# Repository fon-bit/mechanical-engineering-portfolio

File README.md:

# Engineering Portfolio

Welcome! This repository showcases selected ME coursework and personal engineering projects.

Each project folder contains:
- Project Report 
- Supporting files (data, presentations, photos)
- A README with project overview

---

## 📂 Projects

### 🔹 [Capstone Project – Nova Spot Micro 3](Capstone_Project_NovaSpotMicro3/README.md)
- **Objective:** Prototype a quadruped robot using a pre-built frame and motors (Nova SM3)
- **My Role:** 3D modeled the frame in Fusion360/Ansys, ran stress analysis in Ansys, simulated walking in software
- **Tools:** Fusion360, ANSYS, 3D printing  
- **Outcome:** Completed a functional robot prototype capable of walking and surrounding detection  

---

### 🔹 [JanKey40](JanKey40/README.md)
- **Objective:** Create custom keyboard from scratch!
- **Tools:** KiCad, Fusion 360  
- **Deliverables:** Design and create case, pcb, and plate for 40% keyboard!

---

### 🔹 [Transient Simulation](Transient_Simulation/README.md)
- **Objective:** Simulated 2D heat conduction in a material with varying boundary conditions
- **Tools:** ANSYS  
- **Deliverables:** Report how to use transient simulation to show results at specific time and show quantitative results

---

### 🔹 [Bracket Static Structural Study](FEA/README.md)
- **Objective:** Using FEA to analyze a bracket
- **Tools:** ANSYS  
- **Deliverables:** Report showing the understanding of FEA and how to solve for results

---

### 🔹 [Ansys Modal Analysis](Modal_Analysis/README.md)
- **Objective:** Perform a modal analysis on a bracket
- **Tools:** ANSYS
- **Deliverables:** Report showing the understanding of modal analysis and how to solve natural frequencies in a system
  
---

### 🔹 [Fluid CFD Course Project](CFD_Project/README.md)
- **Objective:** Analyze fluid flow and heat transfer in a system. Understand ANSYS software and interpret data results
- **Tools:** ANSYS
- **Deliverables:** Report summarizing data and understanding of CFD

---

## 📬 Contact
Feel free to connect with me on [LinkedIn](https://www.linkedin.com/in/fontanna-vo-6ab0a2368/) or via email: **fontanna_vo@aol.com**.

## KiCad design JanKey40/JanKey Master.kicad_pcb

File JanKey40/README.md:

**JanKey40**

*40% Mechanical Keyboard PCB*

## Overview
This is a personal passion of mine and I've always wanted to try a 40% keyboard and instead of spending $150+ on a prebuilt I decided to spend 150hrs and even more money on building a custom one! All joking aside this has been a passion of mine for a while and I wanted to share with the world my journey in the world of custom keyboards. As of now I'm in the design phase for the case, the pcb is currently under review at the manufactors!! Check at the files and images for this project and feel free to leave me some feedback!

## Objectives
- Designed a custom 40% mechanical keyboard from scratch
- Designed in KiCad, manufacturable PCB (*manufactuered approve*)
- Case design using Fusion360 (*under review @manufactures*)

## Deliverables
- 40% keyboard PCB
- Custom Case Design 
- Final Assembly of keyboard

## 3D Rendered View

https://github.com/user-attachments/assets/bd2a3828-73c8-46a6-a715-73c00b7ea09d

*Case material: anodized aluminum blue (top case) anodized aluminum red (bottom case render)* 

## PHOTOS

**Current files include PCB schematics, pcb and project from KiCad (feel free to download and create your own!)**

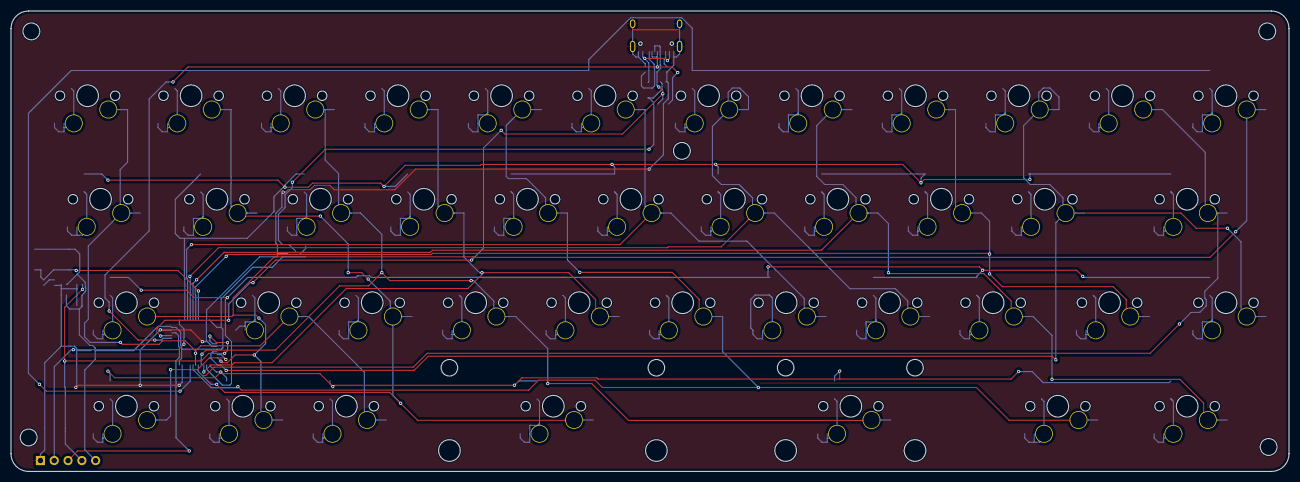
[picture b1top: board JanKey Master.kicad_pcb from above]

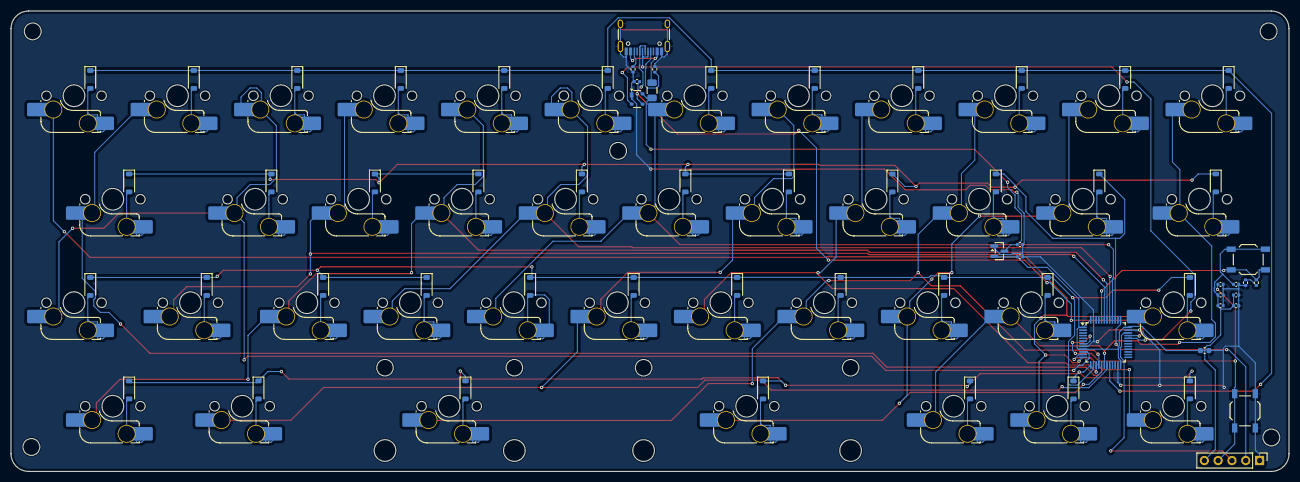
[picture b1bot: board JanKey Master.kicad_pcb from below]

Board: 2 copper layers, 235.2 x 84.8 mm, 111 parts (104 on the bottom side), 70 nets.

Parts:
BOOT1: SW_SPST; SW_SPST_TL3342
C1, C3, C4, C5, C6, C7, C8: 100nF; C_0402_1005Metric
C2: 10uF; C_0603_1608Metric
C9, C10: 1uF; C_0402_1005Metric
D1, D2, D3, D4, D5, D6, D7, D8, D9, D10, D11, D12, D13, D14, D15, D16, D17, D18, D19, D20, D21, D22, D23, D24, D25, D26, D27, D28, D29, D30, D31, D32, D33, D34, D35, D36, D37, D38, D39, D40, D41: D_Small; D_SOD-123
F1: 500mA; Fuse_1206_3216Metric
J1: USB_C_Receptacle_USB2.0; USB_C_Receptacle_HRO_TYPE-C-31-M-12
J2: Conn_01x05; PinHeader_1x05_P2.54mm_Vertical
MX1, MX2, MX3, MX4, MX5, MX6, MX7, MX8, MX9, MX10, MX11, MX12, MX14, MX15, MX16, MX17, MX18, MX19, MX20, MX21, MX22, MX25, MX26, MX27, MX28, MX29, MX30, MX31, MX32, MX34, MX36, MX37, MX38, MX39, MX40, MX41: MX_SW_HS; SW_MX_HS_CPG151101S11_1u
MX13, MX33, MX35: MX_SW_HS; SW_MX_HS_CPG151101S11_1.25u
MX23, MX24: MX_SW_HS; SW_MX_HS_CPG151101S11_1.75u
R1, R2, R3, R4: 5.1k; R_0402_1005Metric
RST1: SW_SPST; SW_SPST_TL3342
S1: MX_stab; STAB_MX_3u
S2: MX_stab; STAB_MX_2.75u
ST1, ST2, ST3, ST4, ST5: Standoff
U1: STM32F072CBT6; LQFP-48_7x7mm_P0.5mm
U2: PRTR5V0U2X; SOT-143
U3: XC6206PxxxMR-Regulator_Linear; SOT-23

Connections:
+3V3: BOOT1.1 (A), C2.1, C3.1, C4.1, C5.1, C6.1, C7.1, C10.1, J2.5, U1.1 (VBAT), U1.9 (VDDA), U1.24 (VDD), U1.36 (VDDIO2), U1.48 (VDD), U3.2 (VO)
+5V: C8.1, C9.1, F1.2, U2.4 (VCC), U3.3 (VI)
BOOT0: BOOT1.2 (B), R3.1, U1.44 (BOOT0)
D+: J1.A6 (D+), J1.B6 (D+), U1.33 (PA12), U2.3 (I/O2)
D-: J1.A7 (D-), J1.B7 (D-), U1.32 (PA11), U2.2 (I/O1)
GND: C1.2, C2.2, C3.2, C4.2, C5.2, C6.2, C7.2, C8.2, C9.2, C10.2, J1.A1 (GND), J1.A12 (GND), J1.B1 (GND), J1.B12 (GND), J1.S1 (SHIELD), J2.1, R1.1, R2.2, R4.2, RST1.2 (B), U1.8 (VSSA), U1.23 (VSS), U1.35 (VSS), U1.47 (VSS), U2.1 (GND), U3.1 (GND)
NRST: C1.1, J2.4, RST1.1 (A), U1.7 (NRST)
unnamed: D1.2 (A), MX1.2
unnamed: D2.2 (A), MX2.2
unnamed: D3.2 (A), MX3.2
unnamed: D4.2 (A), MX4.2
unnamed: D5.2 (A), MX5.2
unnamed: D6.2 (A), MX6.2
unnamed: D7.2 (A), MX7.2
unnamed: D8.2 (A), MX8.2
unnamed: D9.2 (A), MX9.2
unnamed: D10.2 (A), MX10.2
unnamed: D11.2 (A), MX11.2
unnamed: D12.2 (A), MX12.2
unnamed: D13.2 (A), MX13.2
unnamed: D14.2 (A), MX14.2
unnamed: D15.2 (A), MX15.2
unnamed: D16.2 (A), MX16.2
unnamed: D17.2 (A), MX17.2
unnamed: D18.2 (A), MX18.2
unnamed: D19.2 (A), MX19.2
unnamed: D20.2 (A), MX20.2
unnamed: D21.2 (A), MX21.2
unnamed: D22.2 (A), MX22.2
unnamed: D23.2 (A), MX23.2
unnamed: D24.2 (A), MX24.2
unnamed: D25.2 (A), MX25.2
unnamed: D26.2 (A), MX26.2
unnamed: D27.2 (A), MX27.2
unnamed: D28.2 (A), MX28.2
unnamed: D29.2 (A), MX29.2
unnamed: D30.2 (A), MX30.2
unnamed: D31.2 (A), MX31.2
unnamed: D32.2 (A), MX32.2
unnamed: D33.2 (A), MX33.2
unnamed: D34.2 (A), MX34.2
unnamed: D35.2 (A), MX35.2
unnamed: D36.2 (A), MX36.2
unnamed: D37.2 (A), MX37.2
unnamed: D38.2 (A), MX38.2
unnamed: D39.2 (A), MX39.2
unnamed: D40.2 (A), MX40.2
unnamed: D41.2 (A), MX41.2
unnamed: J1.A5 (CC1), R1.2
unnamed: J1.B5 (CC2), R2.1
unnamed: R3.2, R4.1
SWCLK: J2.2, U1.37 (PA14)
SWD: J2.3, U1.34 (PA13)
VBUS: F1.1, J1.A4 (VBUS), J1.A9 (VBUS), J1.B4 (VBUS), J1.B9 (VBUS)
col0: MX1.1, MX13.1, MX25.1, MX37.1, U1.18 (PB0)
col1: MX2.1, MX14.1, MX26.1, MX38.1, U1.17 (PA7)
col2: MX3.1, MX15.1, MX27.1, MX39.1, U1.16 (PA6)
col3: MX4.1, MX16.1, MX28.1, U1.15 (PA5)
col4: MX5.1, MX17.1, MX29.1, MX40.1, U1.19 (PB1)
col5: MX6.1, MX18.1, MX30.1, U1.40 (PB4)
col6: MX7.1, MX19.1, MX31.1, U1.41 (PB5)
col7: MX8.1, MX20.1, MX32.1, MX41.1, U1.42 (PB6)
col8: MX9.1, MX21.1, MX33.1, U1.43 (PB7)
col9: MX10.1, MX22.1, MX34.1, U1.10 (PA0)
col10: MX11.1, MX23.1, MX35.1, U1.11 (PA1)
col11: MX12.1, MX24.1, MX36.1, U1.12 (PA2)
row0: D1.1 (K), D2.1 (K), D3.1 (K), D4.1 (K), D5.1 (K), D6.1 (K), D7.1 (K), D8.1 (K), D9.1 (K), D10.1 (K), D11.1 (K), D12.1 (K), U1.20 (PB2)
row1: D13.1 (K), D14.1 (K), D15.1 (K), D16.1 (K), D17.1 (K), D18.1 (K), D19.1 (K), D20.1 (K), D21.1 (K), D22.1 (K), D23.1 (K), U1.39 (PB3)
row2: D24.1 (K), D25.1 (K), D26.1 (K), D27.1 (K), D28.1 (K), D29.1 (K), D30.1 (K), D31.1 (K), D32.1 (K), D33.1 (K), D34.1 (K), U1.14 (PA4)
row3: D35.1 (K), D36.1 (K), D37.1 (K), D38.1 (K), D39.1 (K), D40.1 (K), D41.1 (K), U1.13 (PA3)

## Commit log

2026-02-03 Create JanKey40
2026-02-03 Rename
2026-02-03 Added PCB Files
